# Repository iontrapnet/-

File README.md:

* 根据文件后缀名进入相应子文件夹，上传文件
* 例如子文件夹名称为pdf，上传文件名称为HelicalResonator.pdf
* 可以通过[http://www.iontrap.net/-/pdf/HelicalResonator.pdf](http://www.iontrap.net/-/pdf/HelicalResonator.pdf)来访问

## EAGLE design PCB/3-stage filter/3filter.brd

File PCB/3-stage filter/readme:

# 三级滤波器

用途：转接高压电源和trap的feedthrough

--qiuxinzhang

*.rar 是提交给cyt制作的压缩文件，里面包含了料单和原件的坐标文件

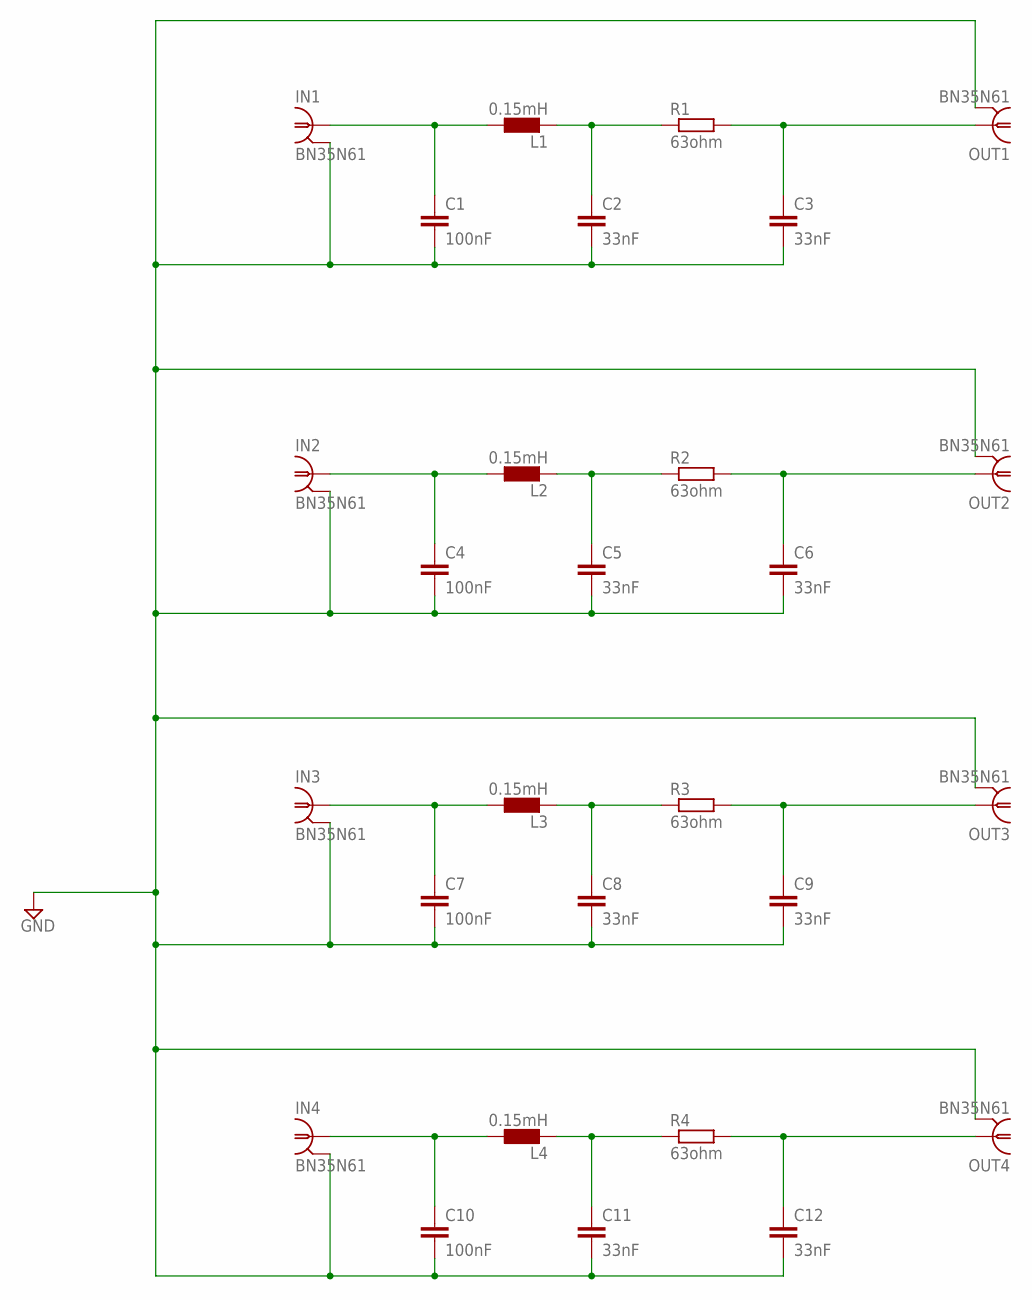
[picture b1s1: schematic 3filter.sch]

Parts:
C1, C4, C7, C10: 100nF; C1210
C2, C3, C5, C6, C8, C9, C11, C12: 33nF; C1210
IN1, IN2, IN3, IN4: BN35N61; B35N61
L1, L2, L3, L4: 0.15mH; L1812
OUT1, OUT2, OUT3, OUT4: BN35N61; B35N61
R1, R2, R3, R4: 63ohm; R0805

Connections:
GND: C1.2, C2.2, C3.2, C4.2, C5.2, C6.2, C7.2, C8.2, C9.2, C10.2, C11.2, C12.2, IN1.2, IN1.3 (2), IN1.4 (2), IN1.5 (2), IN2.2, IN2.3 (2), IN2.4 (2), IN2.5 (2), IN3.2, IN3.3 (2), IN3.4 (2), IN3.5 (2), IN4.2, IN4.3 (2), IN4.4 (2), IN4.5 (2), OUT1.2, OUT1.3 (2), OUT1.4 (2), OUT1.5 (2), OUT2.2, OUT2.3 (2), OUT2.4 (2), OUT2.5 (2), OUT3.2, OUT3.3 (2), OUT3.4 (2), OUT3.5 (2), OUT4.2, OUT4.3 (2), OUT4.4 (2), OUT4.5 (2)
unnamed: C1.1, IN1.1, L1.1
unnamed: C2.1, L1.2, R1.1
unnamed: C3.1, OUT1.1, R1.2
unnamed: C4.1, IN2.1, L2.1
unnamed: C5.1, L2.2, R2.1
unnamed: C6.1, OUT2.1, R2.2
unnamed: C7.1, IN3.1, L3.1
unnamed: C8.1, L3.2, R3.1
unnamed: C9.1, OUT3.1, R3.2
unnamed: C10.1, IN4.1, L4.1
unnamed: C11.1, L4.2, R4.1
unnamed: C12.1, OUT4.1, R4.2

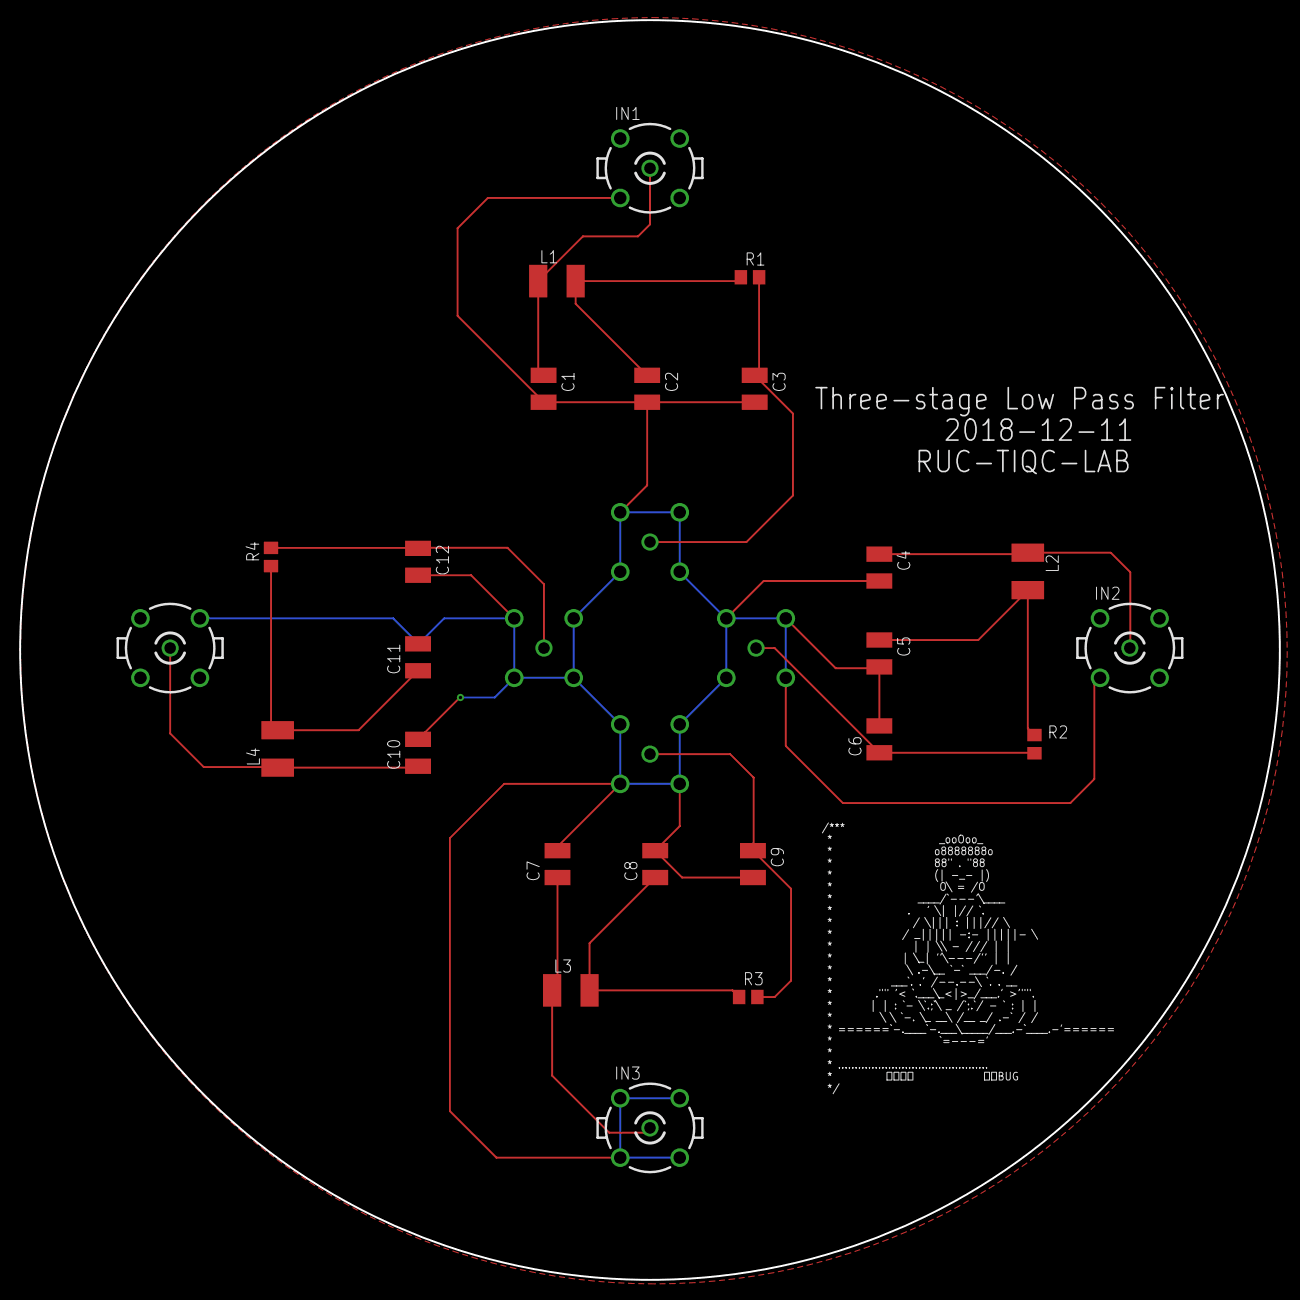
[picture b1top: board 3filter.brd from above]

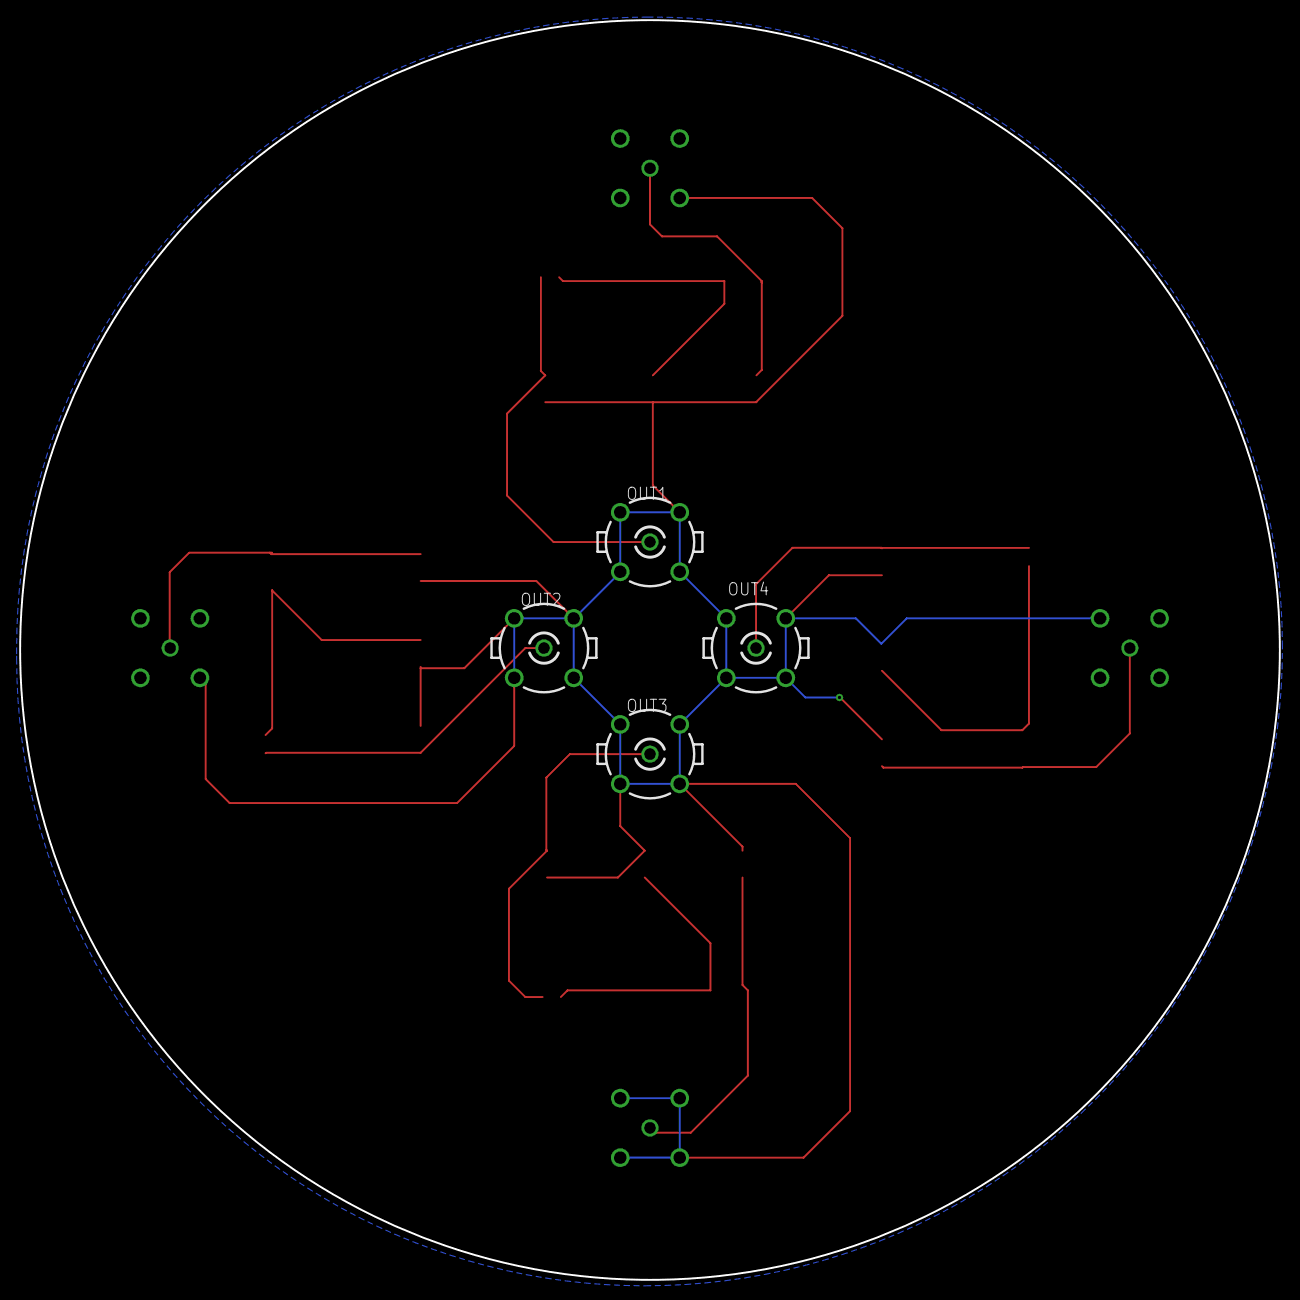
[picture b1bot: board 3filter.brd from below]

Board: 2 copper layers, 131.3 x 131.3 mm, 28 parts (4 on the bottom side), 13 nets.

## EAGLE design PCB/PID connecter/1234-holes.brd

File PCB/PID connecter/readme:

这是用来放置PID电路转接板的文件夹

desginer：qiuxinzhang，siangzhang

1234-holes
代表有4个转接的SMA和一个镂空的长方形洞口。
使用的eagle版本是：EAGLE 8.3.0

<div align="center">

</div>

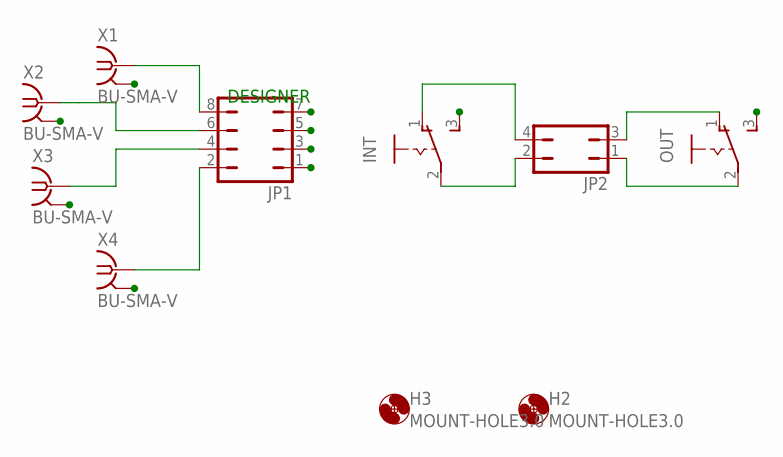
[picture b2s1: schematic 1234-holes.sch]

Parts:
H2, H3: MOUNT-HOLE3.0; 3,0
INT: 255SB
JP1: JP4Q
JP2: JP2Q
OUT: 255SB
X1, X2, X3, X4: BU-SMA-V

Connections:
GND: INT.3 (S), JP1.1, JP1.3, JP1.5, JP1.7, OUT.3 (S), X1.2, X1.3 (2), X1.4 (2), X1.5 (2), X2.2, X2.3 (2), X2.4 (2), X2.5 (2), X3.2, X3.3 (2), X3.4 (2), X3.5 (2), X4.2, X4.3 (2), X4.4 (2), X4.5 (2)
unnamed: INT.2, JP2.2
unnamed: JP1.8, X1.1
unnamed: JP1.6, X2.1
unnamed: INT.1 (O), JP2.4
unnamed: JP1.4, X3.1
unnamed: JP1.2, X4.1
unnamed: JP2.1, OUT.2
unnamed: JP2.3, OUT.1 (O)

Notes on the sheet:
DESIGNER

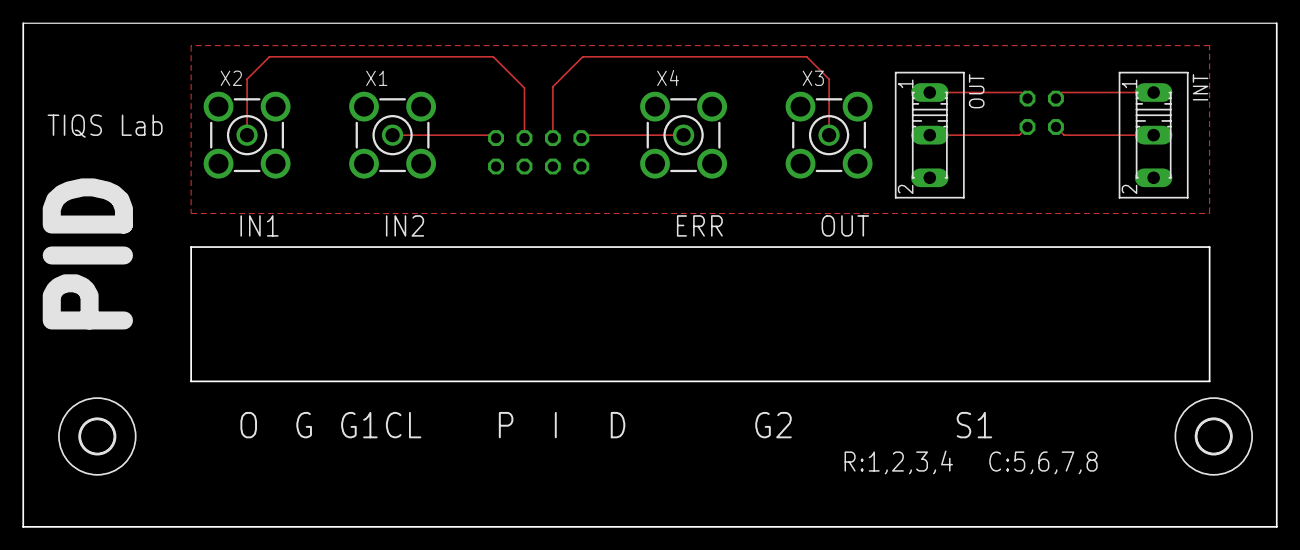
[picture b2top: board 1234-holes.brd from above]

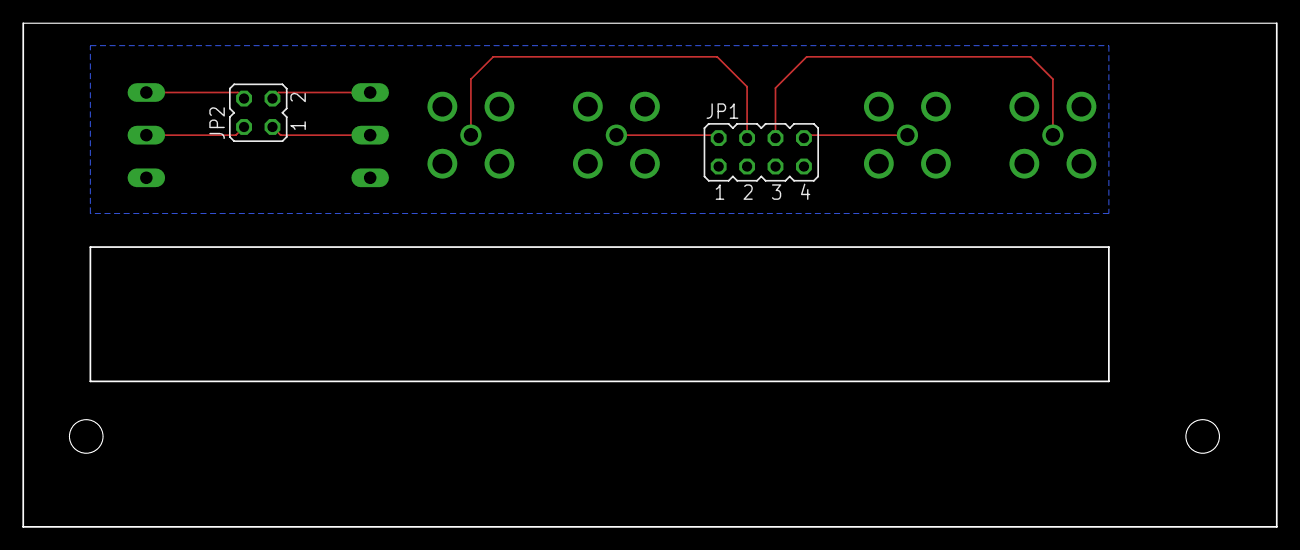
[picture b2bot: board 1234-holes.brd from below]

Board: 2 copper layers, 112.0 x 45.0 mm, 10 parts (2 on the bottom side), 9 nets.

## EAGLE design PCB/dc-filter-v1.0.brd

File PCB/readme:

## 主要用来存放实验室自己制作的简单PCB

- -qiuxinzhang

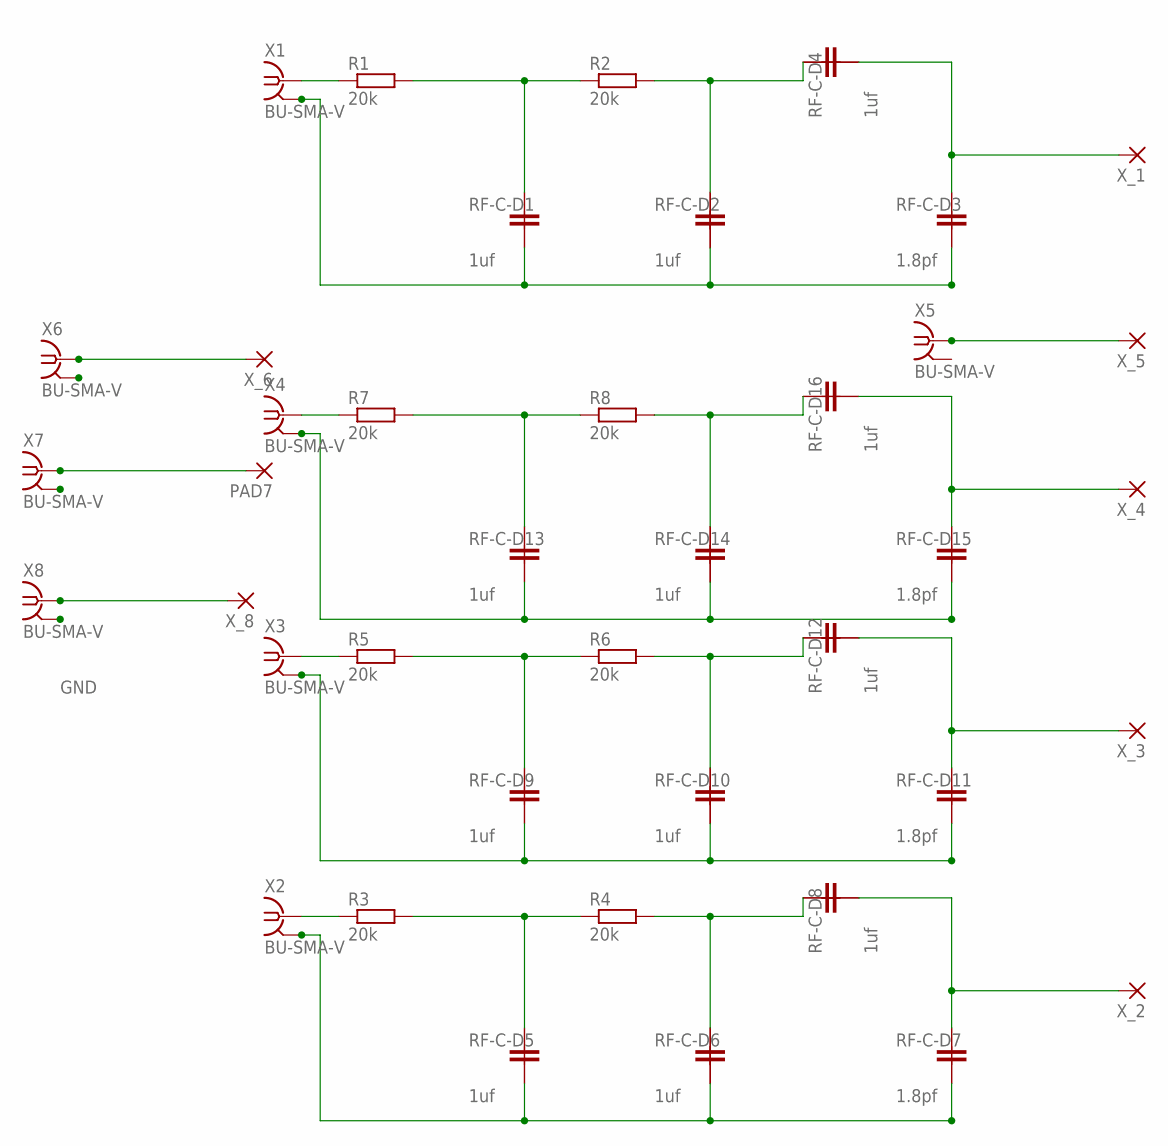
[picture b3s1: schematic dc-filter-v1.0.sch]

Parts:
PAD7: SMD5; SMD2,54-5,08
R1, R2, R3, R4, R5, R6, R7, R8: 20k; R0402
RF-C-D1, RF-C-D2, RF-C-D4, RF-C-D5, RF-C-D6, RF-C-D8, RF-C-D9, RF-C-D10, RF-C-D12, RF-C-D13, RF-C-D14, RF-C-D16: 1uf; 0603
RF-C-D3, RF-C-D7, RF-C-D11, RF-C-D15: 1.8pf; 0603
X1, X2, X3, X4, X5, X6, X7, X8: BU-SMA-V
X_1, X_2, X_3, X_4, X_5, X_6, X_8: SMD5; SMD2,54-5,08

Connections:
GND: RF-C-D1.P$2 (2), RF-C-D2.P$2 (2), RF-C-D3.P$2 (2), RF-C-D5.P$2 (2), RF-C-D6.P$2 (2), RF-C-D7.P$2 (2), RF-C-D9.P$2 (2), RF-C-D10.P$2 (2), RF-C-D11.P$2 (2), RF-C-D13.P$2 (2), RF-C-D14.P$2 (2), RF-C-D15.P$2 (2), X1.2, X1.3 (2), X1.4 (2), X1.5 (2), X2.2, X2.3 (2), X2.4 (2), X2.5 (2), X3.2, X3.3 (2), X3.4 (2), X3.5 (2), X4.2, X4.3 (2), X4.4 (2), X4.5 (2), X6.2, X6.3 (2), X6.4 (2), X6.5 (2), X7.2, X7.3 (2), X7.4 (2), X7.5 (2), X8.2, X8.3 (2), X8.4 (2), X8.5 (2)
unnamed: R1.2, R2.1, RF-C-D1.P$1 (1)
unnamed: R2.2, RF-C-D2.P$1 (1), RF-C-D4.P$1 (1)
unnamed: R3.2, R4.1, RF-C-D5.P$1 (1)
unnamed: R1.1, X1.1
unnamed: RF-C-D3.P$1 (1), RF-C-D4.P$2 (2), X_1.1
unnamed: R4.2, RF-C-D6.P$1 (1), RF-C-D8.P$1 (1)
unnamed: R3.1, X2.1
unnamed: RF-C-D7.P$1 (1), RF-C-D8.P$2 (2), X_2.1
unnamed: R5.2, R6.1, RF-C-D9.P$1 (1)
unnamed: R6.2, RF-C-D10.P$1 (1), RF-C-D12.P$1 (1)
unnamed: R5.1, X3.1
unnamed: RF-C-D11.P$1 (1), RF-C-D12.P$2 (2), X_3.1
unnamed: R7.2, R8.1, RF-C-D13.P$1 (1)
unnamed: R8.2, RF-C-D14.P$1 (1), RF-C-D16.P$1 (1)
unnamed: R7.1, X4.1
unnamed: RF-C-D15.P$1 (1), RF-C-D16.P$2 (2), X_4.1
unnamed: X5.1, X_5.1
unnamed: X6.1, X_6.1
unnamed: PAD7.1, X7.1
X_10: X8.1, X_8.1

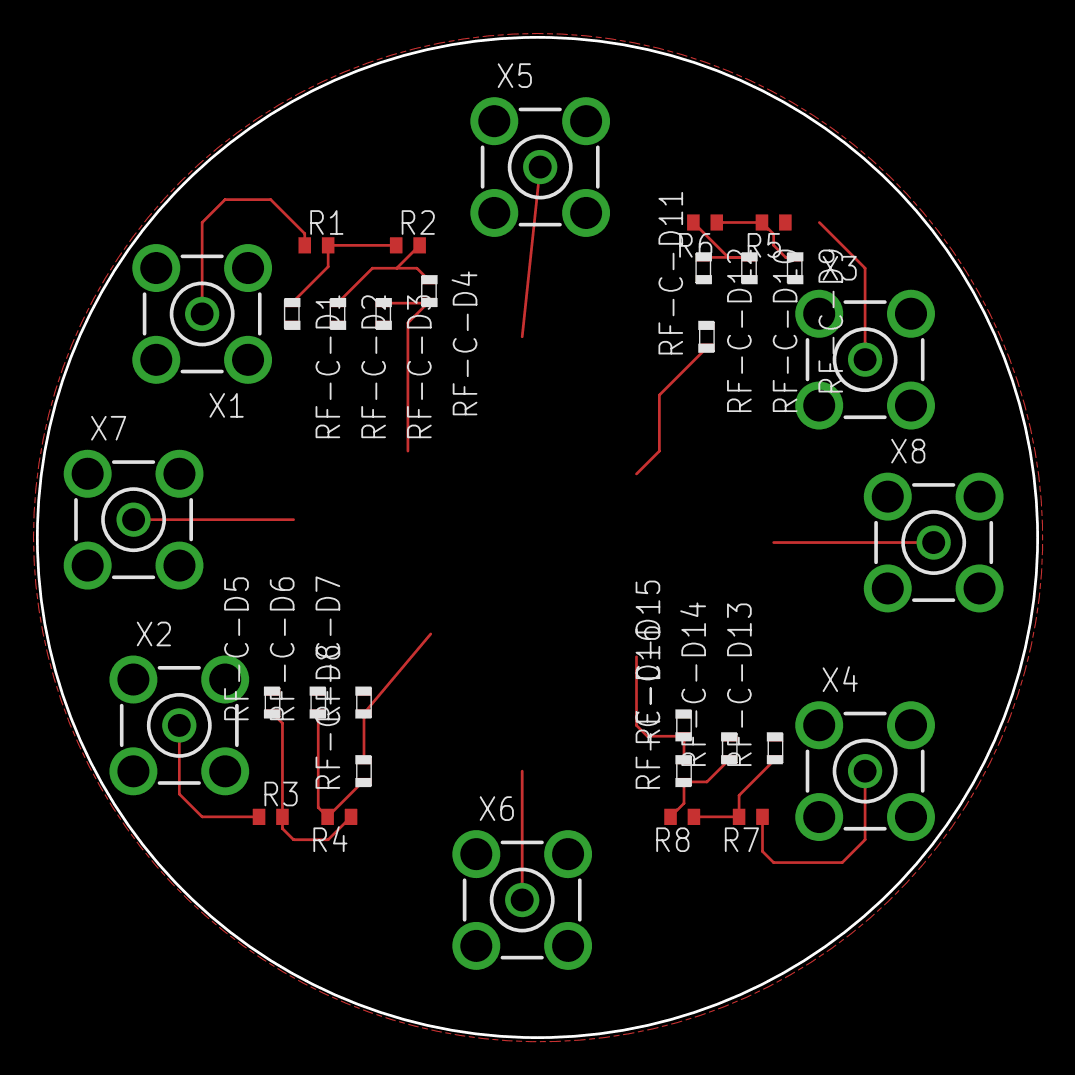
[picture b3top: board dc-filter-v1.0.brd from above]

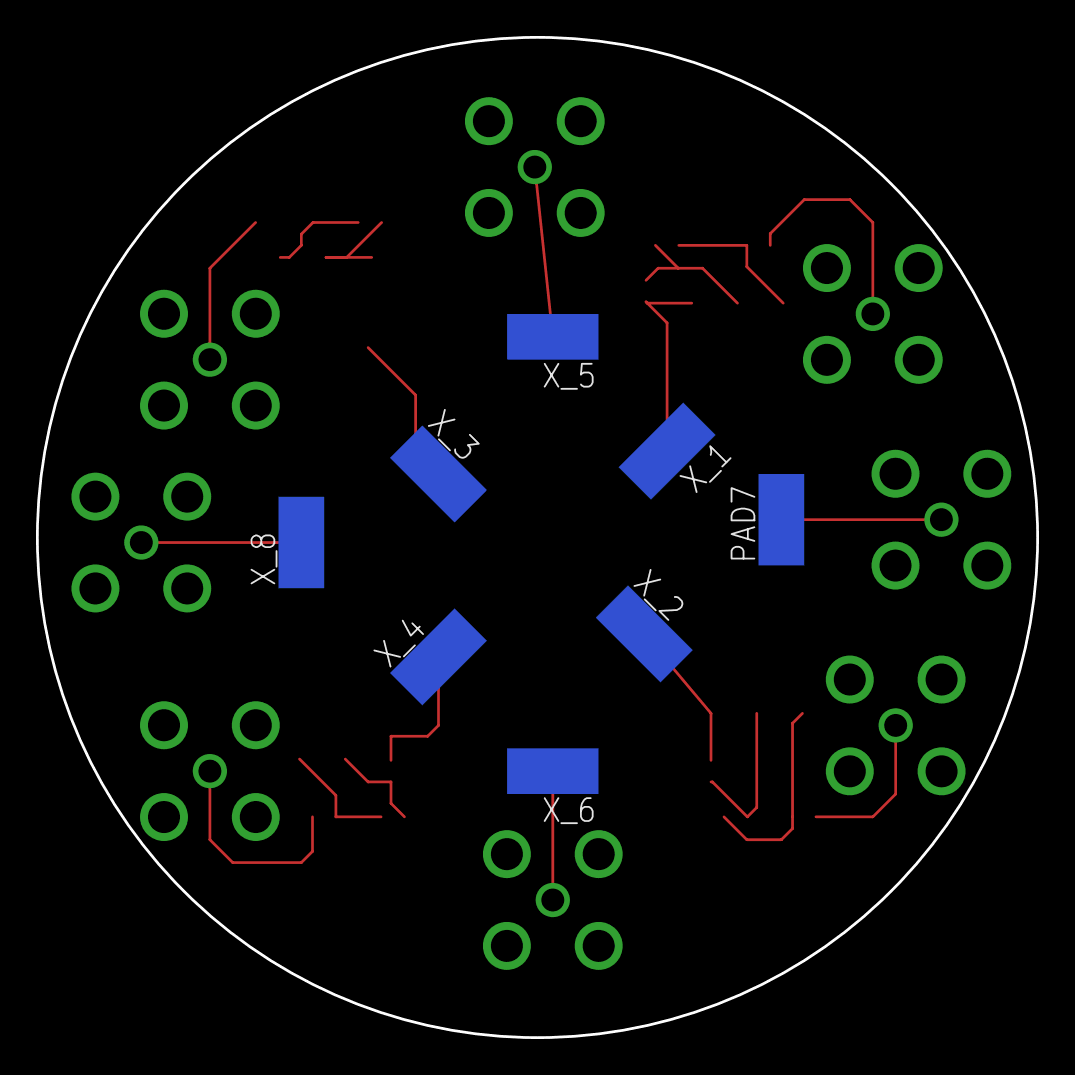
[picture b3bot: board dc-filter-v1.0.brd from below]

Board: 2 copper layers, 55.6 x 55.6 mm, 40 parts (8 on the bottom side), 21 nets.

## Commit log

2017-10-11 add Helical Resonator
2017-10-11 add folders
2017-10-11 change README to utf-8
2017-10-14 Create md
2017-10-21 Add blade trap related designs
2017-10-21 Add two vacuum system designs
2017-10-22 Group meeting 10.23
2017-10-22 add something about long working distance objective
2017-10-29 About AOD & EOD
2017-11-28 change pic to img
2017-11-28 change from pic to img
2017-12-06 knife edge method to measure beam waist
2017-12-11 Upload chamber and 4-rod trap pictures
2017-12-13 Frequency stabilization with Hollow Cathode Lamp
2018-02-02 Add files via upload
    G3芯片工艺记录-180202
2018-04-26 PID面板
2018-12-17 Create 3-stage fliter
2018-12-21 due连接
